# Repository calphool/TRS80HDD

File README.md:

# TRS80HDD
Repo for TRS-80 Model 1 Drive emulator project

Here we go again.  So after I finished the graphics/sound/communications card, I started working on a new
project.  This time I'm working on interfacing the TRS-80 to a Teensy 3.6, which is an Arduino-ish microcontroller 
board.  It's a lot faster than the Arduino Uno, and has more ports.  You can use the Arduino tool chain, which is 
nice. 

Theory of Operation
===================

To understand how this card works (in theory... still working out some bugs as of December 2018), you have to 
understand how the TRS-80 expected to interface to floppy drives.  I'm in awe of what engineers in 1977 had to 
deal with to produce a working computer.  We take so much for granted today.  First of all, the TRS-80 Model 1
couldn't interface to a floppy drive unless you purchased the Expansion System.  That expansion system is 
essentially a large daughter board and a power supply.  It connected to your TRS-80 via a ribbon cable attached 
to the expansion bus on the keyboard/CPU unit.  Inside was a fairly complex set of components.  There's a real time
clock module that keeps pinging the CPU unit 40 times a second.  There's additional DRAM in there.  There's a bunch
of glue logic that allows you to connect a parallel port printer (remember those?) and a UART for (very slow) 
RS232 / modem connectivity.  Finally, there's an [FD1771](https://en.wikipedia.org/wiki/Western_Digital_FD1771) chip.
That chip is one of the first floppy disk controller chips.  It was released in 1976, and was used in various forms 
up into the 1990s.  On one side of the chip you've got an interface designed to connect to a system bus, and on the 
other side you've got an interface designed to connect to a stepper driven floppy drive.  There's glue logic in the 
Expansion System that basically memory mapped the FD1771 chip into the address space of the Z80 processor of the 
CPU unit.  You get a little keyhole interface into RAM (0x37E0 - 0x37EF) that you can read and write to, and the chip 
responds by reading/writing to the floppy by manipulating the drive spindle and the head steppers.

So, the way this emulated device works is that it has an address decoder that watches for those addresses, along with 
read and write signal lines, triggers a flip-flop that puts the Z80 processor in the CPU unit into a WAIT state, 
invokes an interrupt on the Teensy, the Teensy reads an SD card for a disk image, and emulates the intent of the 
read or write command against that disk image file.  Once the read or write is complete the Teensy kicks the flip-flop 
and the WAIT state is released.  ~~At least, that's the theory.  I'm still working through some timing issues before 
I start working in earnest on the Teensy code.  Basically I've got everything working right now except the data bus.
The data bus seems to be doing nothing at the moment, and I haven't figured out exactly what's wrong yet.~~

Build Notes
===========

January 26, 2019

Well, I bodged a 32k SRAM onto the design.  Some NEWDOS games won't work because they expect (quite reasonably) that you have 48k of RAM,
since the original TRS-80 expansion system included some RAM, and you couldn't really run a disk drive without having the extra RAM.  
Version 4.2 of the schematic and board include this enhancement.

So here's what I'm thinking about doing... I'm thinking about designing a set of three stackable boards (sort of like Arduino shields).  The 
first board just gives you 32k of extra RAM, six channel (+2 noise) audio, and your power supply.  The second adds the TMS9118 video 
(see TRS80GS) and joystick ports. The third adds the emulated disk drive.  So, you could build these boards and then snap them together as you like.

January 22, 2019

Holy smokes.  [It's working.](https://www.youtube.com/watch?v=pcdh7HSC1nE)  I've got NEWDOS/80 v2 booting up, and it seems quite functional.  
Since I haven't implemented WRITE handling code, and only the most critical READ handling code, it's pretty fragile right now, but it's booting 
and responding to commands.  This is the v4 board, so if you're following along and want to make your own, v4 with current code is the first 
actually functioning configuration.  

January 16, 2019

Considerable gnashing of teeth has occurred over the past month, but progress has been made.  The v3 and v3.1 designs 
are basically a bust.  There has been some kind of race condition on the WR* side of the data bus, and figuring out what
was going on has been nontrivial.  Folks on the Teensy forum basically said that the problem was that I was using 
unrelated Teensy ports for my 8 data signals, and that digitalReadFast() wasn't fast enough when you used it that way.
So they suggested I redesign the circuit so that all the data lines reside in a single Teensy port, which I did....
and it made absolutely no difference... Luckily I didn't completely trust their diagnosis and I simultaneously created the 
v4 design.  The v4 design was intended to fix the race condition by implementing a latch on the 
data bus (more or less a classical output port design).  This did improve things (actually started getting data to the 
Teensy sometimes), but it wasn't reliable.  After a lot of hand wringing, someone on the Teensy forums suggested a slight 
change to my wait flip flop triggering circuit so that it triggered as soon as an interesting address appeared (as soon 
as the 37EX signal toggled) rather than waiting for both that *and* a RD* or WR* signal.  This made the circuit fairly 
predictable, though it still glitches about 1 out of every 1000 writes.  The design is available in schematic v4.1.
I'm thinking that perhaps if I swap out all the LS series chips with ALS series chips, I'll get just enough of a 
performance boost across the combined propogation delay that I can get the WR* side rock solid like the RD* side is.  We'll
see.

However, the good news is that I'm actually booting stuff now.

~~There's still *some* kind of bug in my emulation, because it gets loaded and then doesn't give me control, and keeps 
trying to reload.  I know that the problem is somehow related to the clock signal, because when I shut it off it loads and
then just sits there.  If I turn it on, it loads, and then reloads, in a loop.  So I'm guessing I need to do something 
besides just turn the clock on, but I don't know what it's expecting just yet.  It could be as simple as making sure that
I'm handling the FD1771 status register correctly when I get to the end of the boot cycle.  I do think I've got a few bugs left 
in the status register handling, and I think I might have an off-by-one problem in handling sector read commands.  So either 
one of those problems could be the source of my rebooting problem.  However, I'm really close, and that makes me super happy.~~

With some help from someone on reddit, I was able to get it booting.  It's related to the fact that I'm using JV1 disk images, 
which apparently don't encode all the data that was on the original disks.  Apparently part of what was missing was a code that 
can be returned in the status register that indicates to the operating system that what it's reading represents directory data.
Since my disk images don't have that info, I guess my code is supposed to assume track 17 is the directory data, so it was 
as simple as forcing the status register to OR 0x20 with whatever it's already doing if the track is 17.

It's still not quite working right, because I can't do a DIR command (says "device not available"), but it's booting and semi-
usable now.  Now I just need to figure out why I can't do a DIR command.  I'm beginning to wonder if I shouldn't just figure 
out how to port the applicable code from SDLTRS over to the Teensy.  Then I'd be able to support several disk formats, and 
these kinds of strange little details would be handled for me, rather than me slowly finding them one by one.  I've avoided 
trying the port exercise, because I wasn't sure if the C compilers are compatible, or if I'll end up with strange data size 
issues or endian issues.  I might make one quick stab at getting it working without the porting effort, and then if it doesn't
work I'll dive into that.

--------------------------------------------------------

December 17, 2018

Well I'm working on version 2 of this project.  I found a copy of Byte Magazine from the late 70s that included a 
schematic from Steve Ciarcia for his Disk-80 project.  I decided to abandon my home grown address decoder and 
switched to his design.  The v3 of the schematic represents that.  Upon assembly, it didn't really work, and I 
was scratching my head.  I reached out to Peter Bartlett, who is the rock star that designed the MISE and M3SE 
boards that are light years beyond what my little projects are capable of.  He took a look at my schematics and 
helped me realize that I used a 74LS241 for my data buffer, and I probably meant to use a 74LS244.  The difference 
is that 74LS241 has four bits that are controlled by a positive enable pin, and the other four are controlled by 
a negative enable pin.  So I ordered some 74LS244's and we'll see where that gets me.

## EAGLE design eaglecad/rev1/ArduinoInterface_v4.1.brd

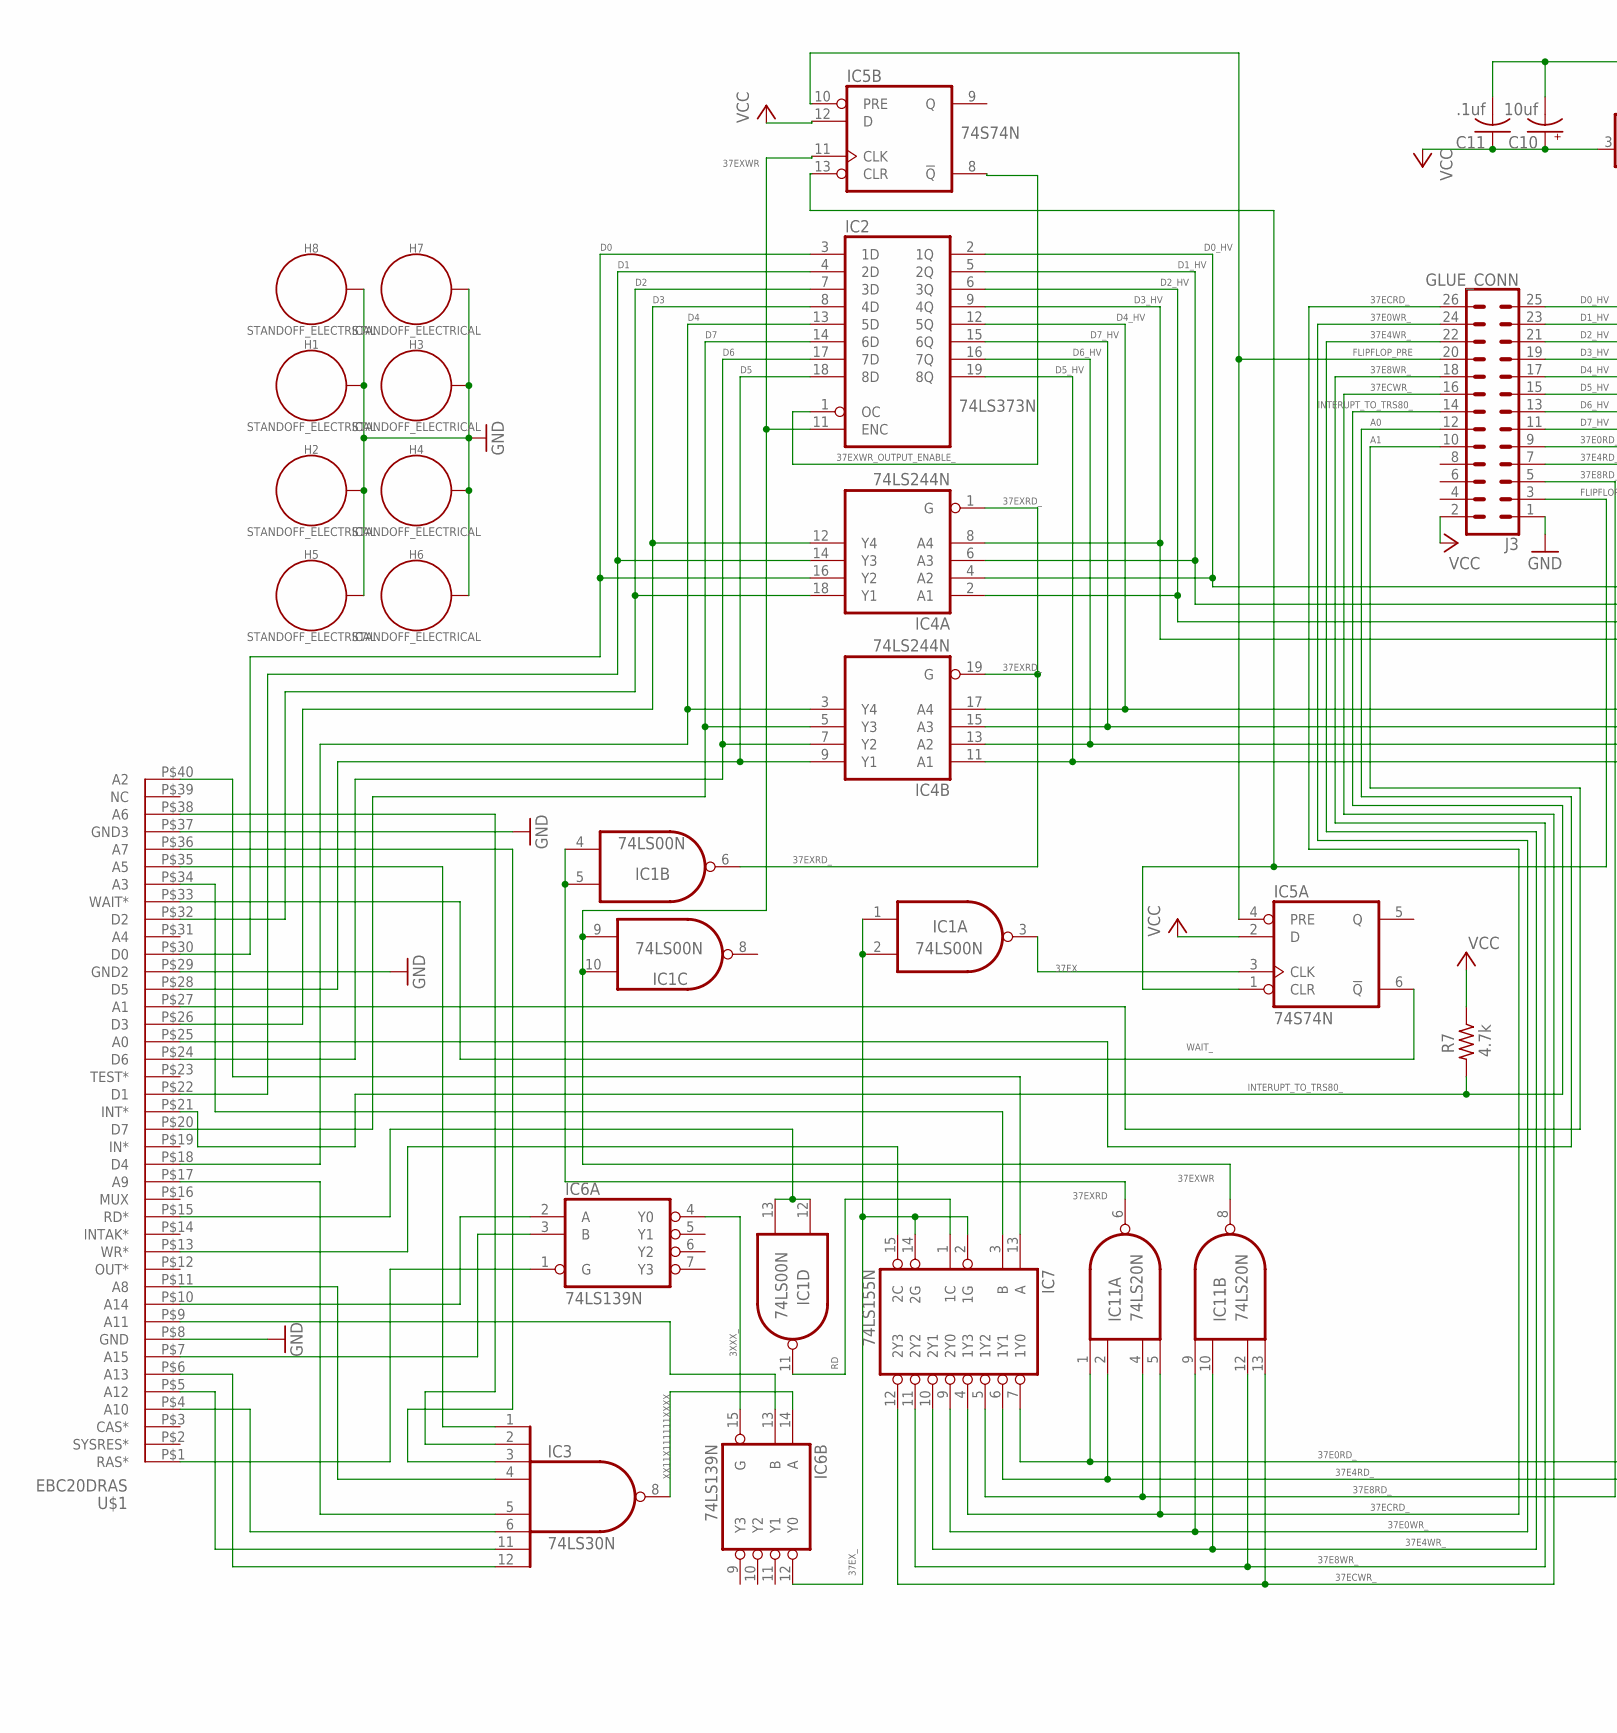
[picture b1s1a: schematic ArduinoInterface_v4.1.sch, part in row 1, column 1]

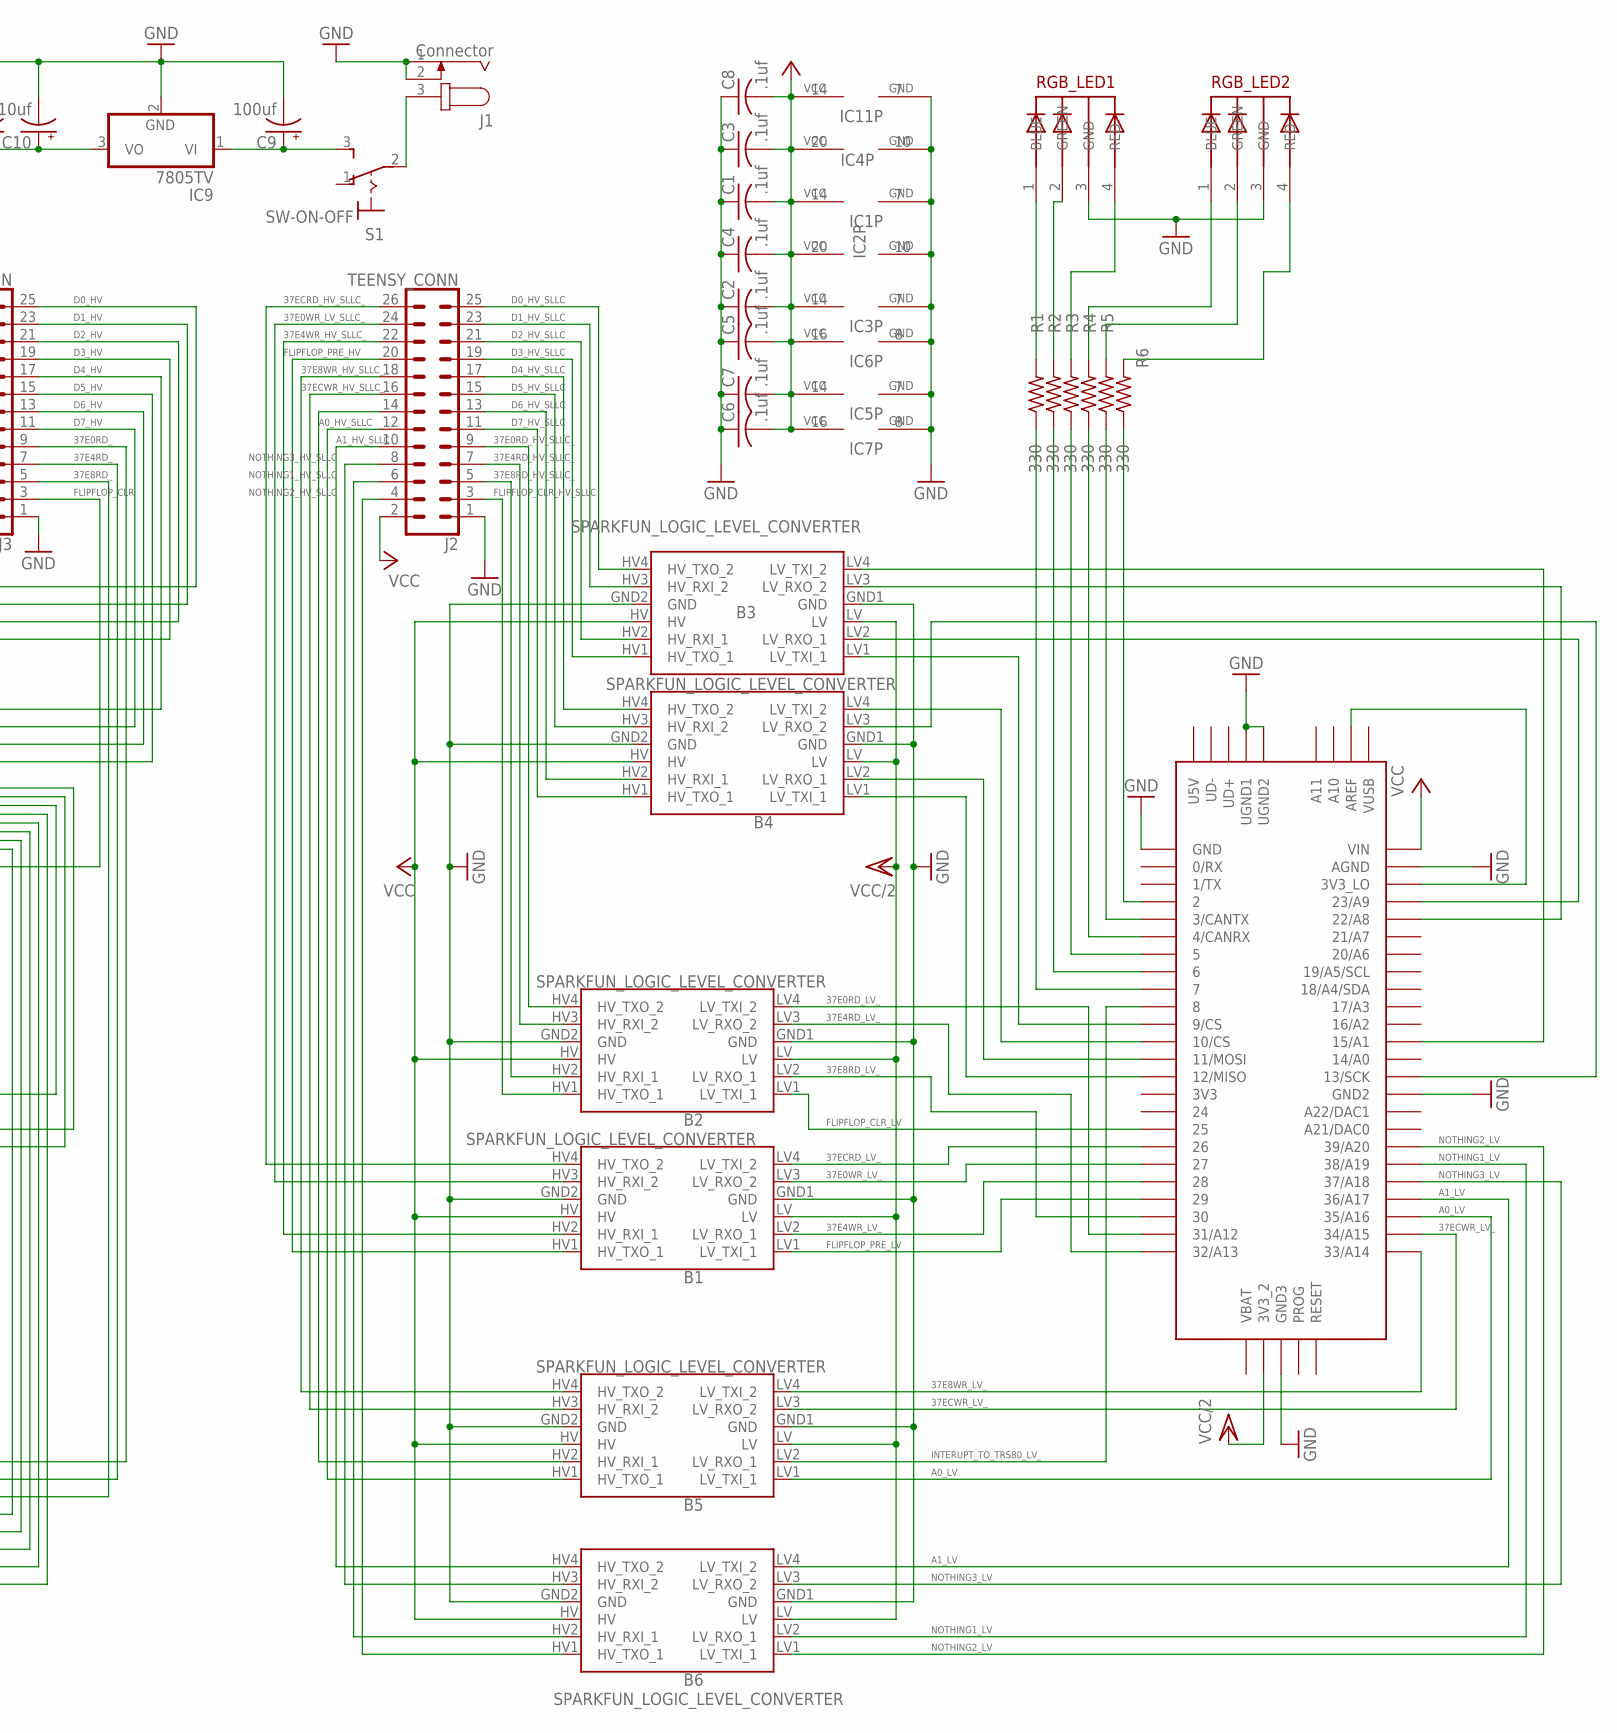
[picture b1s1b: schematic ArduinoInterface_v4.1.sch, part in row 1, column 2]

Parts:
B1, B2, B3, B4, B5, B6: SPARKFUN_LOGIC_LEVEL_CONVERTER
C1, C2, C3, C4, C5, C6, C7, C8, C11: .1uf; C025-025X050
C9: 100uf; E5-6
C10: 10uf; E5-6
H1, H2, H3, H4, H5, H6, H7, H8: STANDOFF_ELECTRICAL; STANDOFF-ELECTRICAL
IC1: 74LS00N; DIL14
IC2: 74LS373N; DIL20
IC3: 74LS30N; DIL14
IC4: 74LS244N; DIL20
IC5: 74S74N; DIL14
IC6: 74LS139N; DIL16
IC7: 74LS155N; DIL16
IC9: 7805TV; TO220V
IC11: 74LS20N; DIL14
J1: Connector; SPC4077
J2: TEENSY_CONN; 2X13
J3: GLUE_CONN; 2X13
R1, R2, R3, R4, R5, R6: 330; 0204V
R7: 4.7k; 0204V
RGB_LED1, RGB_LED2: 5MMRGBLED; LED5MMRGB
S1: SW-ON-OFF; M9040P
U$1: EBC20DRAS
U$2: TEENSY_3.5/3.6

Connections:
3XXX_: IC6.4 (Y0), IC6.15 (G)
9V: C9.+, IC9.1 (VI), S1.3 (S)
9V_TO_SW: J1.3, S1.2
37E0RD_: IC7.7 (1Y0), IC11.1 (I0), J3.9
37E0RD_HV_SLLC_: B2.HV4 (HV_TXO_2), J2.9
37E0RD_LV_: B2.LV4 (LV_TXI_2), U$2.31/A12
37E0WR_: IC7.9 (2Y0), IC11.9 (I0), J3.24
37E0WR_LV_: B1.LV3 (LV_RXO_2), U$2.27
37E0WR_LV_SLLC_: B1.HV3 (HV_RXI_2), J2.24
37E4RD_: IC7.6 (1Y1), IC11.2 (I1), J3.7
37E4RD_HV_SLLC_: B2.HV3 (HV_RXI_2), J2.7
37E4RD_LV_: B2.LV3 (LV_RXO_2), U$2.32/A13
37E4WR_: IC7.10 (2Y1), IC11.10 (I1), J3.22
37E4WR_HV_SLLC_: B1.HV2 (HV_RXI_1), J2.22
37E4WR_LV_: B1.LV2 (LV_RXO_1), U$2.28
37E8RD_: IC7.5 (1Y2), IC11.4 (I2), J3.5
37E8RD_HV_SLLC_: B2.HV2 (HV_RXI_1), J2.5
37E8RD_LV_: B2.LV2 (LV_RXO_1), U$2.30
37E8WR_: IC7.11 (2Y2), IC11.12 (I2), J3.18
37E8WR_HV_SLLC_: B5.HV4 (HV_TXO_2), J2.18
37E8WR_LV_: B5.LV4 (LV_TXI_2), U$2.33/A14
37ECRD_: IC7.4 (1Y3), IC11.5 (I3), J3.26
37ECRD_HV_SLLC_: B1.HV4 (HV_TXO_2), J2.26
37ECRD_LV_: B1.LV4 (LV_TXI_2), U$2.26
37ECWR_: IC7.12 (2Y3), IC11.13 (I3), J3.16
37ECWR_HV_SLLC_: B5.HV3 (HV_RXI_2), J2.16
37ECWR_LV_: B5.LV3 (LV_RXO_2), U$2.34/A15
37EX: IC1.3 (O), IC5.3 (CLK)
37EXRD: IC1.4 (I0), IC1.5 (I1), IC11.6 (O)
37EXRD_: IC1.6 (O), IC4.1 (G), IC4.19 (G)
37EXWR: IC1.9 (I0), IC1.10 (I1), IC2.11 (ENC), IC5.11 (CLK), IC11.8 (O)
37EXWR_OUTPUT_ENABLE_: IC2.1 (OC), IC5.8 (!Q)
37EX_: IC1.1 (I0), IC1.2 (I1), IC6.12 (Y0), IC7.2 (1G), IC7.14 (2G)
A0: J3.12, U$1.P$25 (A0)
A0_HV_SLLC: B5.HV1 (HV_TXO_1), J2.12
A0_LV: B5.LV1 (LV_TXI_1), U$2.35/A16
A1: J3.10, U$1.P$27 (A1)
A1_HV_SLLC: B6.HV4 (HV_TXO_2), J2.10
A1_LV: B6.LV4 (LV_TXI_2), U$2.36/A17
A2: IC7.13 (A), U$1.P$40 (A2)
A3: IC7.3 (B), U$1.P$34 (A3)
A5: IC3.1 (I0), U$1.P$35 (A5)
A6: IC3.2 (I1), U$1.P$38 (A6)
A7: IC3.3 (I2), U$1.P$36 (A7)
A8: IC3.4 (I3), U$1.P$11 (A8)
A9: IC3.5 (I4), U$1.P$17 (A9)
A10: IC3.6 (I5), U$1.P$4 (A10)
A11: IC6.13 (B), U$1.P$9 (A11)
A12: IC3.11 (I6), U$1.P$5 (A12)
A13: IC3.12 (I7), U$1.P$6 (A13)
A14: IC6.2 (A), U$1.P$10 (A14)
A15: IC6.3 (B), U$1.P$7 (A15)
D0: IC2.3 (1D), IC4.16 (Y2), U$1.P$30 (D0)
D0_HV: IC2.2 (1Q), IC4.4 (A2), J3.25
D0_HV_SLLC: B3.HV4 (HV_TXO_2), J2.25
D0_LV: B3.LV4 (LV_TXI_2), U$2.15/A1
D1: IC2.4 (2D), IC4.14 (Y3), U$1.P$22 (D1)
D1_HV: IC2.5 (2Q), IC4.6 (A3), J3.23
D1_HV_SLLC: B3.HV3 (HV_RXI_2), J2.23
D1_LV: B3.LV3 (LV_RXO_2), U$2.22/A8
D2: IC2.7 (3D), IC4.18 (Y1), U$1.P$32 (D2)
D2_HV: IC2.6 (3Q), IC4.2 (A1), J3.21
D2_HV_SLLC: B3.HV2 (HV_RXI_1), J2.21
D2_LV: B3.LV2 (LV_RXO_1), U$2.23/A9
D3: IC2.8 (4D), IC4.12 (Y4), U$1.P$26 (D3)
D3_HV: IC2.9 (4Q), IC4.8 (A4), J3.19
D3_HV_SLLC: B3.HV1 (HV_TXO_1), J2.19
D3_LV: B3.LV1 (LV_TXI_1), U$2.9/CS
D4: IC2.13 (5D), IC4.3 (Y4), U$1.P$18 (D4)
D4_HV: IC2.12 (5Q), IC4.17 (A4), J3.17
D4_HV_SLLC: B4.HV4 (HV_TXO_2), J2.17
D4_LV: B4.LV4 (LV_TXI_2), U$2.10/CS
D5: IC2.18 (8D), IC4.9 (Y1), U$1.P$28 (D5)
D5_HV: IC2.19 (8Q), IC4.11 (A1), J3.15
D5_HV_SLLC: B4.HV3 (HV_RXI_2), J2.15
D5_LV: B4.LV3 (LV_RXO_2), U$2.13/SCK
D6: IC2.17 (7D), IC4.7 (Y2), U$1.P$24 (D6)
D6_HV: IC2.16 (7Q), IC4.13 (A2), J3.13
D6_HV_SLLC: B4.HV2 (HV_RXI_1), J2.13
D6_LV: B4.LV2 (LV_RXO_1), U$2.11/MOSI
D7: IC2.14 (6D), IC4.5 (Y3), U$1.P$20 (D7)
D7_HV: IC2.15 (6Q), IC4.15 (A3), J3.11
D7_HV_SLLC: B4.HV1 (HV_TXO_1), J2.11
D7_LV: B4.LV1 (LV_TXI_1), U$2.12/MISO
FLIPFLOP_CLR: IC5.1 (CLR), IC5.13 (CLR), J3.3
FLIPFLOP_CLR_HV_SLLC: B2.HV1 (HV_TXO_1), J2.3
FLIPFLOP_CLR_LV: B2.LV1 (LV_TXI_1), U$2.25
FLIPFLOP_PRE: IC5.4 (PRE), IC5.10 (PRE), J3.20
FLIPFLOP_PRE_HV: B1.HV1 (HV_TXO_1), J2.20
FLIPFLOP_PRE_LV: B1.LV1 (LV_TXI_1), U$2.29
GND: B1.GND1 (GND), B1.GND2 (GND), B2.GND1 (GND), B2.GND2 (GND), B3.GND1 (GND), B3.GND2 (GND), B4.GND1 (GND), B4.GND2 (GND), B5.GND1 (GND), B5.GND2 (GND), B6.GND1 (GND), B6.GND2 (GND), C1.1, C2.1, C3.1, C4.1, C5.1, C6.1, C7.1, C8.1, C9.-, C10.-, C11.2, H1.P1, H2.P1, H3.P1, H4.P1, H5.P1, H6.P1, H7.P1, H8.P1, IC1.7 (GND), IC2.10 (GND), IC3.7 (GND), IC4.10 (GND), IC5.7 (GND), IC6.8 (GND), IC7.8 (GND), IC9.2 (GND), IC11.7 (GND), J1.1, J1.2, J2.1, J3.1, RGB_LED1.3 (GND), RGB_LED2.3 (GND), U$1.P$8 (GND), U$1.P$29 (GND2), U$1.P$37 (GND3), U$2.AGND, U$2.GND, U$2.GND2, U$2.GND3, U$2.UGND1, U$2.UGND2
INTERUPT_TO_TRS80_: J3.14, R7.2, U$1.P$21 (INT*)
INTERUPT_TO_TRS80_HV_SLLC_: B5.HV2 (HV_RXI_1), J2.14
INTERUPT_TO_TRS80_LV_: B5.LV2 (LV_RXO_1), U$2.8
unnamed: U$2.3V3_LO, U$2.AREF
unnamed: R2.2, RGB_LED1.2 (GREEN)
unnamed: R6.1, U$2.2
unnamed: R5.1, U$2.3/CANTX
unnamed: R4.1, U$2.4/CANRX
unnamed: R3.1, U$2.5
unnamed: R2.1, U$2.6
unnamed: R1.1, U$2.7
unnamed: R1.2, RGB_LED1.1 (BLUE)
unnamed: R3.2, RGB_LED1.4 (RED)
unnamed: R4.2, RGB_LED2.1 (BLUE)
unnamed: R5.2, RGB_LED2.2 (GREEN)
unnamed: R6.2, RGB_LED2.4 (RED)
NOTHING1_HV_SLLC: B6.HV2 (HV_RXI_1), J2.6
NOTHING1_LV: B6.LV2 (LV_RXO_1), U$2.38/A19
NOTHING2_HV_SLLC: B6.HV1 (HV_TXO_1), J2.4
NOTHING2_LV: B6.LV1 (LV_TXI_1), U$2.39/A20
NOTHING3_HV_SLLC: B6.HV3 (HV_RXI_2), J2.8
NOTHING3_LV: B6.LV3 (LV_RXO_2), U$2.37/A18
RAS_: IC6.1 (G), U$1.P$1 (RAS*)
RD: IC1.11 (O), IC7.1 (1C)
RD_: IC1.12 (I0), IC1.13 (I1), U$1.P$15 (RD*)
VCC: B1.HV, B2.HV, B3.HV, B4.HV, B5.HV, B6.HV, C1.2, C2.2, C3.2, C4.2, C5.2, C6.2, C7.2, C8.2, C10.+, C11.1, IC1.14 (VCC), IC2.20 (VCC), IC3.14 (VCC), IC4.20 (VCC), IC5.2 (D), IC5.12 (D), IC5.14 (VCC), IC6.16 (VCC), IC7.16 (VCC), IC9.3 (VO), IC11.14 (VCC), J2.2, J3.2, R7.1, U$2.VIN
VCC/2: B1.LV, B2.LV, B3.LV, B4.LV, B5.LV, B6.LV, U$2.3V3_2
WAIT_: IC5.6 (!Q), U$1.P$33 (WAIT*)
WR_: IC7.15 (2C), U$1.P$13 (WR*)
XX11X111111XXXX: IC3.8 (O), IC6.14 (A)

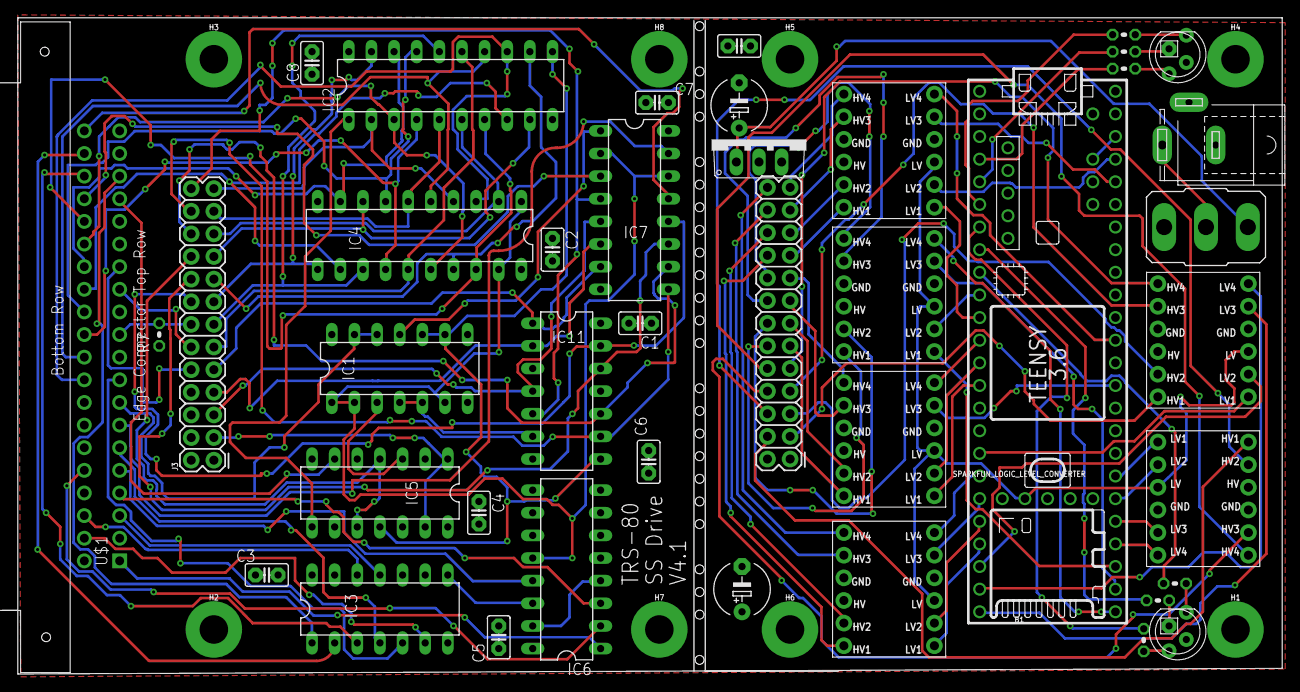
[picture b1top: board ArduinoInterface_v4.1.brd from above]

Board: 2 copper layers, 141.9 x 73.6 mm, 49 parts (0 on the bottom side), 121 nets.

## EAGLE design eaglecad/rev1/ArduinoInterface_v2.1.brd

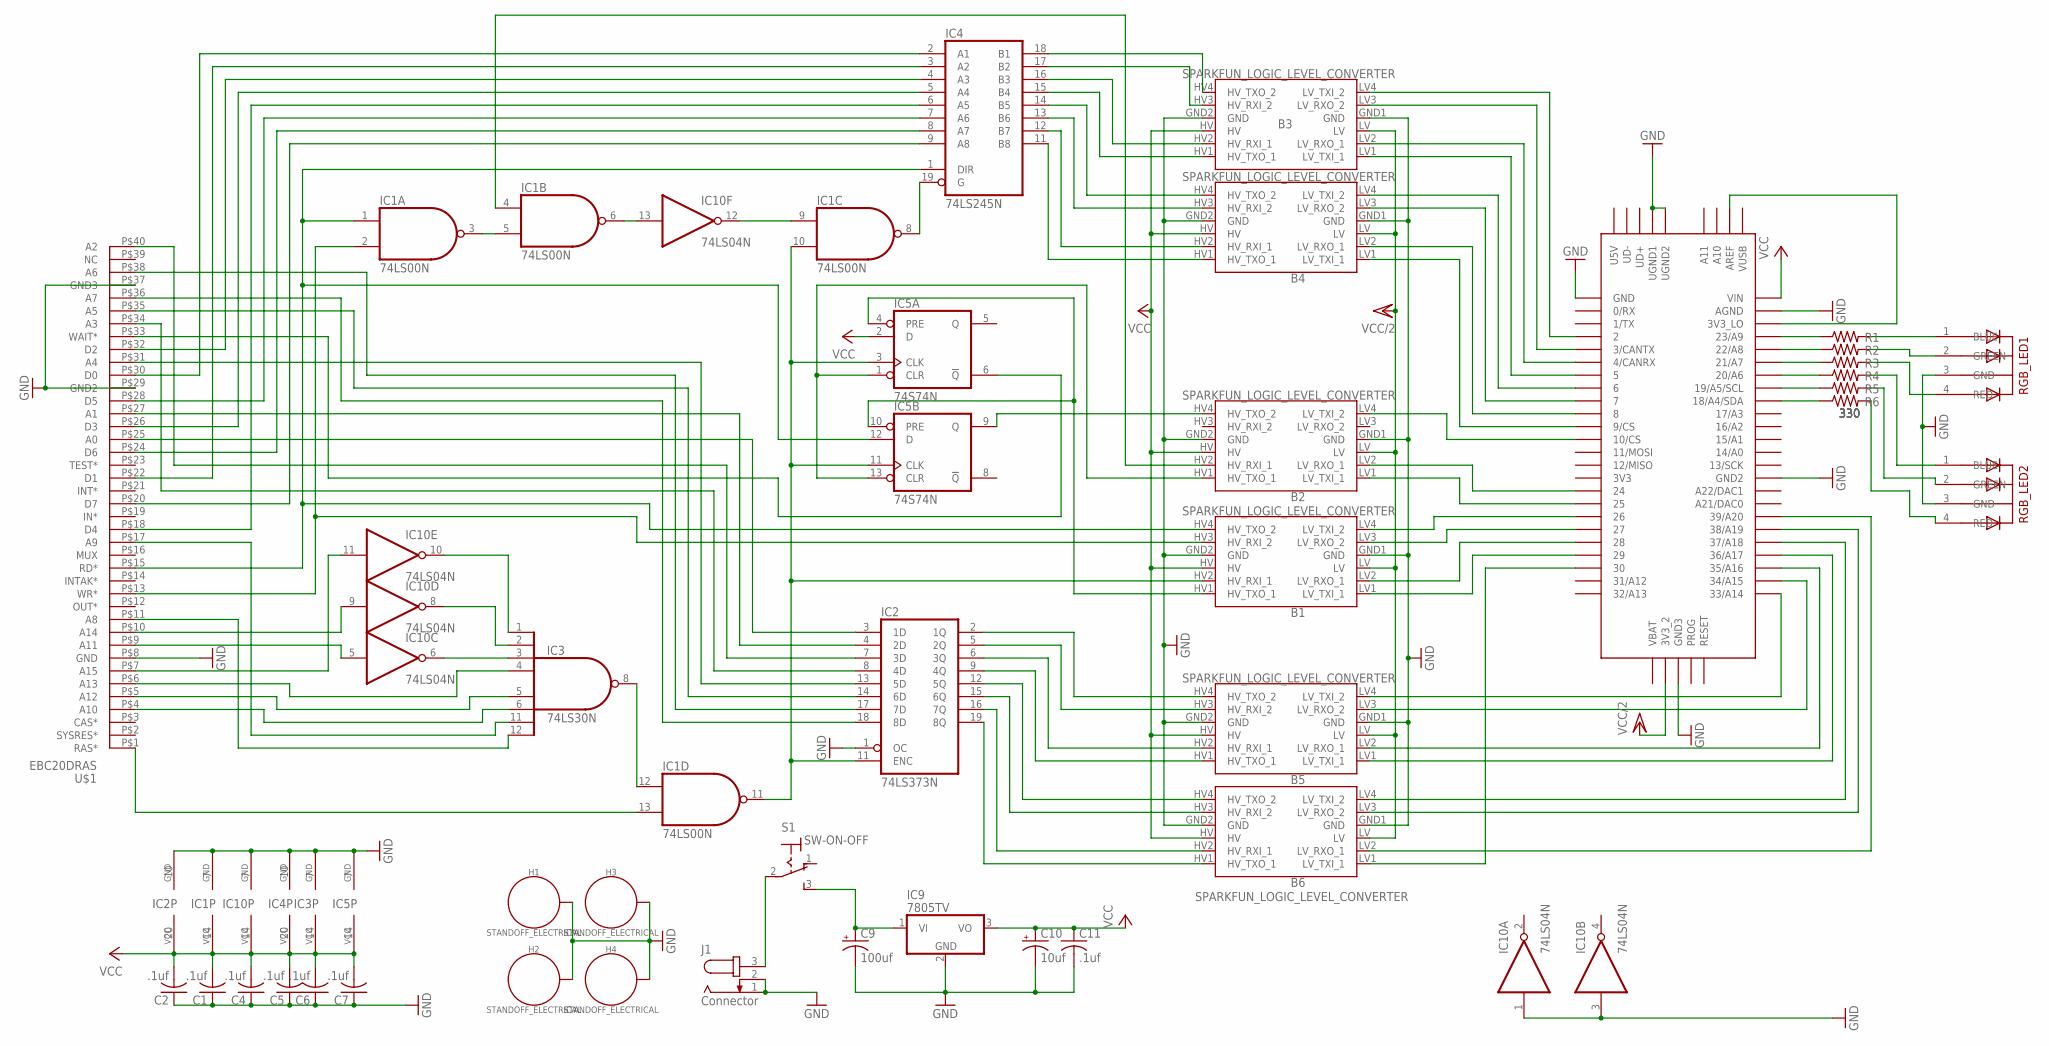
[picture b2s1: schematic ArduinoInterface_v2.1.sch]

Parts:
B1, B2, B3, B4, B5, B6: SPARKFUN_LOGIC_LEVEL_CONVERTER
C1, C2, C4, C5, C6, C7, C11: .1uf; C025-025X050
C9: 100uf; E5-6
C10: 10uf; E5-6
H1, H2, H3, H4: STANDOFF_ELECTRICAL; STANDOFF-ELECTRICAL
IC1: 74LS00N; DIL14
IC2: 74LS373N; DIL20
IC3: 74LS30N; DIL14
IC4: 74LS245N; DIL20
IC5: 74S74N; DIL14
IC9: 7805TV; TO220V
IC10: 74LS04N; DIL14
J1: Connector; SPC4077
R1, R2, R3, R4, R5, R6: 330; 0204V
RGB_LED1, RGB_LED2: 5MMRGBLED; LED5MMRGB
S1: SW-ON-OFF; M9040P
U$1: EBC20DRAS
U$2: TEENSY_3.5/3.6

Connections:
A0: IC2.3 (1D), U$1.P$25 (A0)
A0_AFTER_LATCH: B5.HV4 (HV_TXO_2), IC2.2 (1Q)
A0_LV: B5.LV4 (LV_TXI_2), U$2.33/A14
A1: IC2.4 (2D), U$1.P$27 (A1)
A1_AFTER_LATCH: B5.HV3 (HV_RXI_2), IC2.5 (2Q)
A1_LV: B5.LV3 (LV_RXO_2), U$2.34/A15
A2: IC2.7 (3D), U$1.P$40 (A2)
A2_AFTER_LATCH: B5.HV2 (HV_RXI_1), IC2.6 (3Q)
A2_LV: B5.LV2 (LV_RXO_1), U$2.35/A16
A3: IC2.8 (4D), U$1.P$34 (A3)
A3_AFTER_LATCH: B5.HV1 (HV_TXO_1), IC2.9 (4Q)
A3_LV: B5.LV1 (LV_TXI_1), U$2.36/A17
A4: IC2.13 (5D), U$1.P$31 (A4)
A4_AFTER_LATCH: B6.HV4 (HV_TXO_2), IC2.12 (5Q)
A4_LV: B6.LV4 (LV_TXI_2), U$2.37/A18
A5: IC2.14 (6D), U$1.P$35 (A5)
A5_AFTER_LATCH: B6.HV3 (HV_RXI_2), IC2.15 (6Q)
A5_LV: B6.LV3 (LV_RXO_2), U$2.38/A19
A6: IC2.17 (7D), U$1.P$38 (A6)
A6_AFTER_LATCH: B6.HV2 (HV_RXI_1), IC2.16 (7Q)
A6_LV: B6.LV2 (LV_RXO_1), U$2.39/A20
A7: IC2.18 (8D), U$1.P$36 (A7)
A7_AFTER_LATCH: B6.HV1 (HV_TXO_1), IC2.19 (8Q)
A7_LV: B6.LV1 (LV_TXI_1), U$2.30
A8: IC3.12 (I7), U$1.P$11 (A8)
A9: IC3.11 (I6), U$1.P$17 (A9)
A10: IC3.6 (I5), U$1.P$4 (A10)
A11: IC10.5 (I), U$1.P$9 (A11)
A12: IC3.5 (I4), U$1.P$5 (A12)
A13: IC3.4 (I3), U$1.P$6 (A13)
A15: IC10.11 (I), U$1.P$7 (A15)
D0: IC4.2 (A1), U$1.P$30 (D0)
D0_LV: B3.LV4 (LV_TXI_2), U$2.2
D1: IC4.3 (A2), U$1.P$22 (D1)
D1_LV: B3.LV3 (LV_RXO_2), U$2.3/CANTX
D2: IC4.4 (A3), U$1.P$32 (D2)
D2_HV: B3.HV2 (HV_RXI_1), IC4.16 (B3)
D2_LV: B3.LV2 (LV_RXO_1), U$2.4/CANRX
D3: IC4.5 (A4), U$1.P$26 (D3)
D3_HV: B3.HV1 (HV_TXO_1), IC4.15 (B4)
D3_LV: B3.LV1 (LV_TXI_1), U$2.5
D4: IC4.6 (A5), U$1.P$18 (D4)
D4_HV: B4.HV4 (HV_TXO_2), IC4.14 (B5)
D4_LV: B4.LV4 (LV_TXI_2), U$2.6
D5: IC4.7 (A6), U$1.P$28 (D5)
D5_HV: B4.HV3 (HV_RXI_2), IC4.13 (B6)
D5_LV: B4.LV3 (LV_RXO_2), U$2.7
D6: IC4.8 (A7), U$1.P$24 (D6)
D6_HV: B4.HV2 (HV_RXI_1), IC4.12 (B7)
D6_LV: B4.LV2 (LV_RXO_1), U$2.8
D7: IC4.9 (A8), U$1.P$20 (D7)
D7_HV: B4.HV1 (HV_TXO_1), IC4.11 (B8)
D7_LV: B4.LV1 (LV_TXI_1), U$2.9/CS
DATA_BUS_ENABLE_: IC1.8 (O), IC4.19 (G)
DATA_BUS_ENABLE_HV_FROM_TEENSY: B2.HV2 (HV_RXI_1), IC1.4 (I0)
DATA_BUS_ENABLE_LV: B2.LV2 (LV_RXO_1), U$2.24
FLIPFLOP_CLR: B2.HV1 (HV_TXO_1), IC5.1 (CLR), IC5.13 (CLR)
FLIPFLOP_CLR_LV: B2.LV1 (LV_TXI_1), U$2.25
FLIPFLOP_PRE: B1.HV1 (HV_TXO_1), IC5.4 (PRE), IC5.10 (PRE)
FLIPFLOP_PRE_LV: B1.LV1 (LV_TXI_1), U$2.29
GND: B1.GND1 (GND), B1.GND2 (GND), B2.GND1 (GND), B2.GND2 (GND), B3.GND1 (GND), B3.GND2 (GND), B4.GND1 (GND), B4.GND2 (GND), B5.GND1 (GND), B5.GND2 (GND), B6.GND1 (GND), B6.GND2 (GND), C1.1, C2.1, C4.1, C5.1, C6.1, C7.1, C9.-, C10.-, C11.2, H1.P1, H2.P1, H3.P1, H4.P1, IC1.7 (GND), IC2.1 (OC), IC2.10 (GND), IC3.7 (GND), IC4.10 (GND), IC5.7 (GND), IC9.2 (GND), IC10.1 (I), IC10.3 (I), IC10.7 (GND), J1.1, J1.2, RGB_LED1.3 (GND), RGB_LED2.3 (GND), U$1.P$8 (GND), U$1.P$29 (GND2), U$1.P$37 (GND3), U$2.AGND, U$2.GND, U$2.GND2, U$2.GND3, U$2.UGND1, U$2.UGND2
INTERRUPT: B1.HV2 (HV_RXI_1), IC1.10 (I1), IC1.11 (O), IC2.11 (ENC), IC5.3 (CLK), IC5.11 (CLK)
INTERRUPT_LV: B1.LV2 (LV_RXO_1), U$2.28
unnamed: U$2.3V3_LO, U$2.AREF
unnamed: IC10.9 (I), U$1.P$10 (A14)
unnamed: IC3.1 (I0), IC10.10 (O)
unnamed: IC3.2 (I1), IC10.8 (O)
unnamed: R1.1, U$2.23/A9
unnamed: R2.1, U$2.22/A8
unnamed: IC1.12 (I0), IC3.8 (O)
unnamed: IC3.3 (I2), IC10.6 (O)
unnamed: R3.1, U$2.21/A7
unnamed: R1.2, RGB_LED1.1 (BLUE)
unnamed: C9.+, IC9.1 (VI), S1.3 (S)
unnamed: B3.HV4 (HV_TXO_2), IC4.18 (B1)
unnamed: R2.2, RGB_LED1.2 (GREEN)
unnamed: R3.2, RGB_LED1.4 (RED)
unnamed: R4.1, U$2.20/A6
unnamed: R5.1, U$2.19/A5/SCL
unnamed: R6.1, U$2.18/A4/SDA
unnamed: R4.2, RGB_LED2.1 (BLUE)
unnamed: R5.2, RGB_LED2.2 (GREEN)
unnamed: R6.2, RGB_LED2.4 (RED)
unnamed: J1.3, S1.2
unnamed: B3.HV3 (HV_RXI_2), IC4.17 (B2)
unnamed: IC1.13 (I1), U$1.P$1 (RAS*)
RDX_OR_WRX_AND_DATA_BUS_ENABLE_FROM_TEENSY: IC1.9 (I0), IC10.12 (O)
RDX_OR_WRX_AND_DATA_BUS_ENABLE_FROM_TEENSY_: IC1.6 (O), IC10.13 (I)
RD_: B1.HV4 (HV_TXO_2), IC1.1 (I0), IC4.1 (DIR), IC5.12 (D), U$1.P$15 (RD*)
RD_LV_: B1.LV4 (LV_TXI_2), U$2.26
READ_OR_WRITE: IC1.3 (O), IC1.5 (I1)
VCC: B1.HV, B2.HV, B3.HV, B4.HV, B5.HV, B6.HV, C1.2, C2.2, C4.2, C5.2, C6.2, C7.2, C10.+, C11.1, IC1.14 (VCC), IC2.20 (VCC), IC3.14 (VCC), IC4.20 (VCC), IC5.2 (D), IC5.14 (VCC), IC9.3 (VO), IC10.14 (VCC), U$2.VIN
VCC/2: B1.LV, B2.LV, B3.LV, B4.LV, B5.LV, B6.LV, U$2.3V3_2
WAIT_: IC5.6 (!Q), U$1.P$33 (WAIT*)
WR_: B1.HV3 (HV_RXI_2), IC1.2 (I1), U$1.P$13 (WR*)
WR_HV: B2.HV4 (HV_TXO_2), IC5.9 (Q)
WR_LV: B2.LV4 (LV_TXI_2), U$2.10/CS
WR_LV_: B1.LV3 (LV_RXO_2), U$2.27

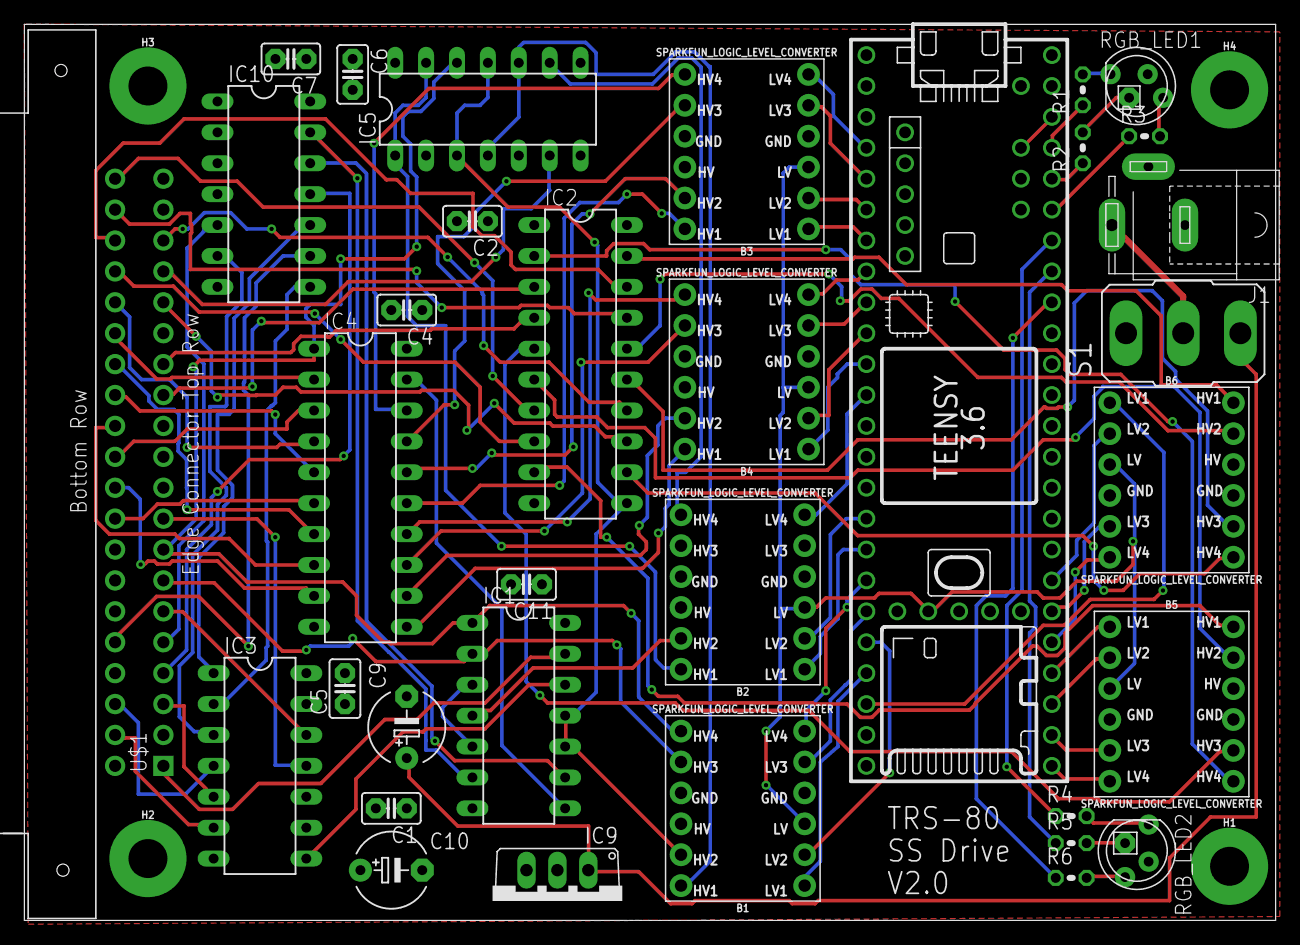
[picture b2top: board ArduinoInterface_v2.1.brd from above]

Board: 2 copper layers, 102.8 x 73.6 mm, 38 parts (0 on the bottom side), 98 nets.

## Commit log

2018-10-31 eaglecad drawings
2018-10-31 teensy code - initial
2018-10-31 add documents
2018-10-31 teensy code
2018-12-01 fixed spelling
2018-12-17 changes to Teensy code
2018-12-17 remove old file
2018-12-17 TeensyDiskEmu update
2018-12-18 updating schematics
2018-12-18 added disassembly book
2018-12-18 updated schematic to fix 74LS241/74LS244 mixup
2018-12-24 updating code to current state - sort of working, RD* side seems to be working, WR* side not quite
2018-12-28 updated code... working... sort of
2019-01-04 current work v3.0 code
2019-01-05 updates to v4 schematic
2019-01-11 update for v3.1 of schematic
2019-01-13 work on v4 with logs
2019-01-13 fix for status register differences
2019-01-13 adding disk-80 article to docs
2019-01-13 adding trs-80 schematic
2019-01-13 added Z80 reference
2019-01-14 updated log file
2019-01-14 update for v4.1 of board and current code
2019-01-16 current state, stable but a little buggy, almost boots successfully
2019-01-16 readme
2019-01-17 update pic
2019-01-19 current status, almost working
2019-01-22 syncing... still struggling, but getting closer
2019-01-23 Got it booting::: yay
2019-01-23 it's alive
2019-01-23 clean up readme
2019-01-24 added serial control and multiple drives
2019-01-24 added code for supporting multiple drives
2019-01-27 schematic changes
2019-01-28 Added Mac utility for manipulating TRS80HDD over USB (mount files, catalog disk images, etc.)
2019-01-28 updating code to handle uploading processs. May not work
2019-01-28 minor fix
2019-01-29 trs80util tweaks
2019-01-29 updated utility banner
2019-01-29 working upload code - upload DSK files to TRS80HDD via USB
2019-01-29 update makefile

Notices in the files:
parts and their libraries:
SparkFun-Hardware: Licensing: Creative Commons ShareAlike 4.0 International - https://creativecommons.org/licenses/by-sa/4.0
